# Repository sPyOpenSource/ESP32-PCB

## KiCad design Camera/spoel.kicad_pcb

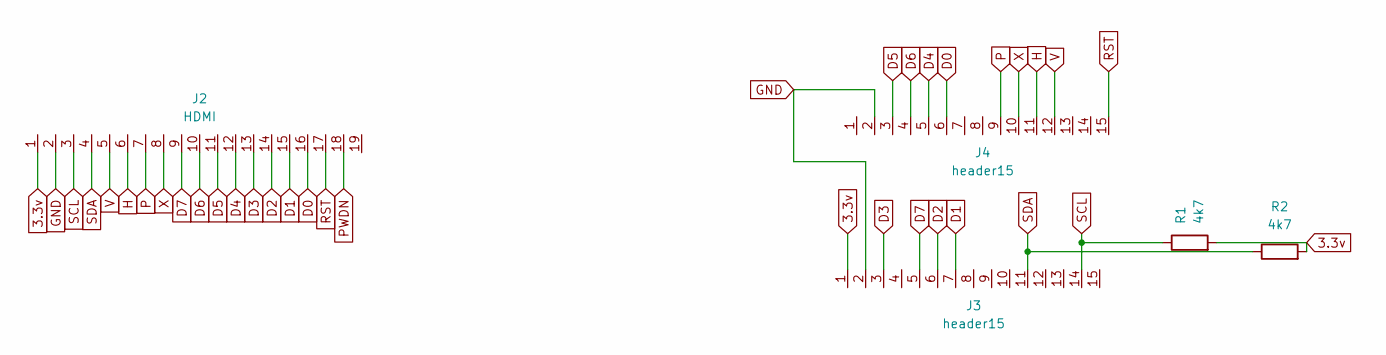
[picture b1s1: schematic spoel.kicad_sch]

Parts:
J2: HDMI; PinSocket_2x09_P2.54mm_Vertical
J3, J4: header15; PinHeader_1x15_P2.54mm_Horizontal
R1, R2: 4k7; R_0603_1608Metric

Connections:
3.3v: J2.1, J3.1, R1.2, R2.2
D0: J2.16, J4.6
D1: J2.15, J3.7
D2: J2.14, J3.6
D3: J2.13, J3.3
D4: J2.12, J4.5
D5: J2.11, J4.3
D6: J2.10, J4.4
D7: J2.9, J3.5
GND: J2.2, J3.2, J4.2
H: J2.6, J4.11
P: J2.7, J4.9
PWDN: J2.18
RST: J2.17, J4.15
SCL: J2.3, J3.14, R1.1
SDA: J2.4, J3.11, R2.1
V: J2.5, J4.12
X: J2.8, J4.10

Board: 4 copper layers, 5 parts (0 on the bottom side), 17 nets, no tracks yet.

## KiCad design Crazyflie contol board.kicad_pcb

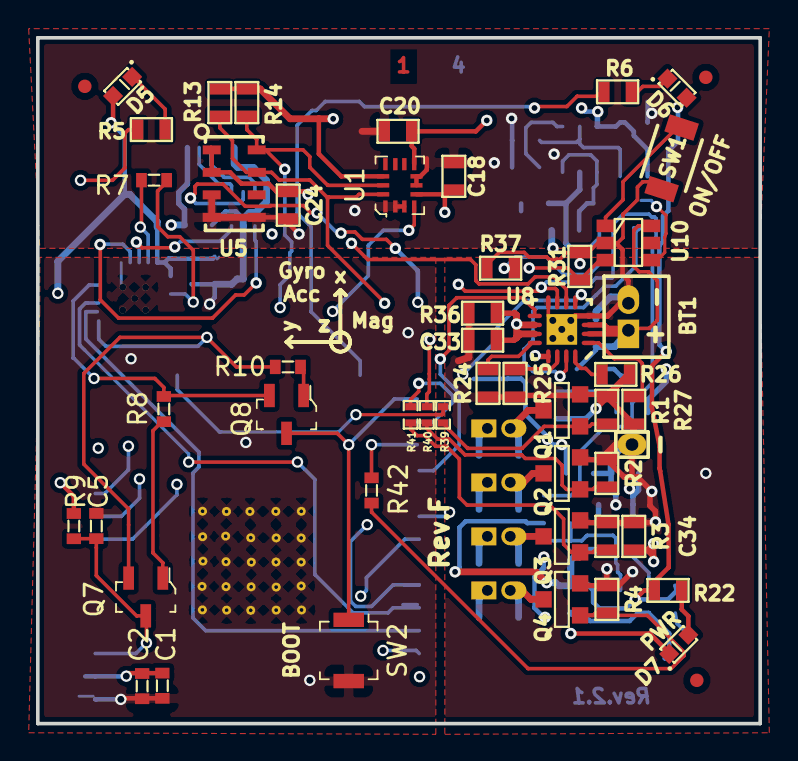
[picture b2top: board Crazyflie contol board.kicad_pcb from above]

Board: 4 copper layers, 40.1 x 38.1 mm, 92 parts (0 on the bottom side), 62 nets.

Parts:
BT1: BATTERY; JST-B2B-ZR
C1: 22uF; 0603_new_new
C2, C3, C5: 100nF; 0603_new_new
C4, C30, C31, C34, C37: 4.7uF; SM0603_Capa
C18, C20, C24, C33, C36, C38, C41: 100nF; SM0603_Capa
C29, C35: 15pF; SM0603_Capa
C32, C40: 10nF; SM0603_Capa
C39: 10uF; SM0603_Capa
D1, D2, D3, D4: BAT54; sod323
D5: RED LED; SMDLED-0603
D6: GREEN LED; SMDLED-0603
D7, D8: BLUE LED; SMDLED-0603
P1, P2, P3, P4: CONN_2; PINHEADER_127_2X1
P7: MICRO-B-USB; ZX62-B-5PA_11_CFK
P9: CONN_1; PINHEADER_127_1X1
Q1, Q2, Q3, Q4: PMV31XN; SOT23GDS
Q5, Q6: 2N7002; SOT23GDS
Q7, Q8: SS8050-G; SOT-23-3
R1, R2, R3, R4, R25, R27, R32, R33, R36, R37: 10k; SM0603
R5: 330R; SM0603
R6: 220R; SM0603
R7: 1k; 0603_new_new
R8, R9, R10: 10k; 0603_new_new
R13, R14: 2.2k; SM0603
R16: 39k; SM0603
R17: 10R; SM0603
R18, R28: 30k; SM0603
R19, R29: 0R; SM0603
R20: 42.2k; SM0603
R21: 300k; SM0603
R22, R38: 1k; SM0603
R23: 150k; SM0603
R24: 1.2k; SM0603
R26: 1.2K; SM0603
R30: 20k; SM0603
R31: 100k; SM0603
R39, R40, R41: 100R; SM0402
R42: 100R; 0603_new_new
SW1: PUSH ON/OFF; SPST-NO-4x2.5
SW2: BOOT; Switch_Tactile_SMD_B3U-1000P_new_new
U1: BMX160; LGA-14L_2.5x3mm__LSM6DS3
U5: MS5611-01BA03; MS5611
U6: NUF2221; SOT363
U7, U9: TPS79301; SOT23_6
U8: BQ24075; QFN16
U10: MAX16054; SOT23_6
U11: ESP32-WROOM; ESP32-WROOM-32_new
U12: CP2102N-A01-GQFN24; QFN-24-1EP_4x4mm_new_new_new

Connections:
+BATT: BT1.1, C39.1, D1.2, D2.2, D3.2, D4.2, P1.1, P2.1, P3.1, P4.1, R30.2, U8.2, U8.3, U10.6
/CHG: U8.9, U11.28
/EN1: U8.6, U11.10
/EN2: U8.5, U11.12
/I2C_SCK_VCCA: R13.2, U1.14, U5.7, U11.33
/I2C_SCL_VCCA: R14.2, U1.13, U5.8, U11.36
/INT_GA: U1.4, U11.9
/MOTOR1: R39.1, U11.16
/MOTOR2: R40.1, U11.37
/MOTOR3: R41.1, U11.26
/MOTOR4: R42.1, U11.27
/PGOOD: R21.1, R23.2, U8.7, U11.30
/POWER/D+: P7.3, U6.6
/POWER/D-: P7.2, U6.4
/POWER/VBAT: C41.1, Q5.S, R32.2
/POWER/VUSB: C36.1, P7.1, Q6.G, R37.2, U8.13
/RED: R5.1, U11.31
/SYSOFF: R31.2, U10.3, U11.8
/USBD+: U6.1, U12.3
/USBD-: U6.3, U12.4
AGND: C18.2, C20.2, C24.2, C30.2, C32.2, R18.1, R19.1, U1.1, U1.2, U1.3, U1.6, U1.7, U5.3, U5.4, U5.5
DGND: C1.2, C2.2, C3.1, C4.1, C5.1, C36.2, C37.2, C40.2, D7.2, D8.2, P7.5, R28.1, R29.1, SW2.2, U6.2, U11.1, U11.15, U11.38, U11.39, U12.2, U12.25
GND: BT1.2, C31.2, C33.2, C34.2, C38.2, C39.2, C41.2, P9.1, Q1.S, Q2.S, Q3.S, Q4.S, Q6.S, R1.2, R2.2, R3.2, R4.2, R19.2, R24.1, R25.1, R26.1, R27.1, R29.2, R31.1, R32.1, R36.1, R37.1, SW1.1, U7.2, U8.4, U8.8, U8.17, U9.2, U10.2
unnamed: C5.2, Q7.3, R9.2, U11.3
unnamed: C29.2, R16.1, R18.2, U7.5
unnamed: C31.1, R17.1, U7.1, U7.3
unnamed: C32.1, U7.4
unnamed: C35.2, R20.1, R23.1, R28.2, U9.5
unnamed: C40.1, U9.4
unnamed: D1.1, P1.2, Q1.D
unnamed: D2.1, P2.2, Q2.D
unnamed: D3.1, P3.2, Q3.D
unnamed: D4.1, P4.2, Q4.D
unnamed: D5.2, R5.2
unnamed: D6.2, R6.2
unnamed: D7.1, R22.1
unnamed: D8.1, R38.1
unnamed: Q1.G, R1.1, R39.2
unnamed: Q2.G, R2.1, R40.2
unnamed: Q3.G, R3.1, R41.2
unnamed: Q4.G, R4.1, R42.2
unnamed: Q5.D, R30.1
unnamed: Q6.D, R33.2, U8.15
unnamed: Q7.1, R8.1
unnamed: Q7.2, R10.1, U12.19
unnamed: Q8.1, R10.2
unnamed: Q8.2, R8.2, U12.23
unnamed: Q8.3, SW2.1, U11.25
unnamed: R6.1, U11.24
unnamed: R7.1, U12.5
unnamed: R7.2, U12.9
unnamed: R24.2, U8.12
unnamed: R25.2, U8.14
unnamed: R26.2, U8.16
unnamed: R27.2, U8.1
unnamed: R33.1, U10.4
unnamed: SW1.2, U10.1
unnamed: U11.34, U12.21
unnamed: U11.35, U12.20
VCC: C1.1, C2.1, C3.2, C4.2, C35.1, C37.1, D5.1, D6.1, R9.1, R20.2, R21.2, R22.2, R38.2, U6.5, U9.6, U11.2, U12.6, U12.7
VCCA: C18.1, C20.1, C24.1, C29.1, C30.1, R13.1, R14.1, R16.2, U1.5, U1.8, U1.12, U5.1, U5.2, U7.6
VCOM: C33.1, C34.1, C38.1, Q5.G, R17.2, R36.2, U8.10, U8.11, U9.1, U9.3

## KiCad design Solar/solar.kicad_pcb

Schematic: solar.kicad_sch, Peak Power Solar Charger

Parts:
C1, C4, C6, C15: 0.1uF; 0603
C2: 220uF; Cpol-6.3x7.7
C3: 100uF; Cpol-6.3x7.7
C5: 1nF; 0603
D1: D_Schottky; DO-214AC
D5: COMMS; 0603
IC1: MAX4173H
J1: SOLAR_INPUT; 1210
J2: Left; PIN16
J3: Right; PIN16
J4: BATTERY_OUTPUT; 1210
J5: header3; PIN2
J6: in; 1210
J7: SOLAR_OUTPUT; 1210
L2: 33uH; 7447779139
Q2: IRFIZ44N; SOT-223
R1, R2, R12: 10k; 0603
R3, R13, R14: 560R; 0603
R4: 100R; 0603
R7: 0.005R; 0603
R9: 4K7; R_0805_HandSoldering
R10: 220R; 0603
RX1: Receive; JST_PH_S2B-PH-K_02x2.00mm_Angled
RX2: Receive; PIN2
TX1: Transmit; JST_PH_S2B-PH-K_02x2.00mm_Angled
U1: HMHA2801; SOP-4_4.4x2.8mm_Pitch1.27mm
U2: MAX5424; TDFN-8-1EP

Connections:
+3V3: C1.1, IC1.1 (VCC), J3.1, RX1.2, U2.1
Bat+: C2.1, J4.1 (Bat+), J6.2, L2.2, R12.2; also elsewhere on the board
GND: C1.2, C2.2, C3.2, C4.2, C5.1, C6.2, C15.2, D1.2 (A), D5.1 (K), IC1.3 (GND), J1.2 (Sol-), J2.15, J3.2, J4.2 (Bat-), J6.1, J7.1 (Bat+), R1.2, R3.1, R9.1, R13.1, RX2.2, U1.2, U2.5; also elsewhere on the board
I_Sol: C4.1, IC1.4 (OUT), J2.6
unnamed: C5.2, Q2.1 (G), R1.1, R4.1
unnamed: D1.1 (K), L2.1, Q2.3 (S)
unnamed: D5.2 (A), R14.1
unnamed 7: IC1.8 (RS+), J1.1 (Sol+), R2.2, R7.1; also elsewhere on the board
unnamed: J2.12, U2.2
unnamed: J2.14, U2.3
unnamed: J3.3, U2.4
unnamed: J3.5, R14.2
unnamed: J3.10, RX2.1
unnamed: J3.12, R9.2, RX1.1
unnamed: J3.13, R10.2
unnamed: J5.1, U2.6
unnamed: J5.2, J5.6, U2.7
unnamed: J5.3, U2.8
unnamed: R10.1, U1.1
unnamed: TX1.1, U1.3
unnamed: TX1.2, U1.4
PWM: J3.15, R4.2
Solar+: C3.1, IC1.6 (RS-), J2.16, J7.2 (Bat-), Q2.2 (D), R7.2; also elsewhere on the board
U_Bat: C15.1, J2.8, R12.1, R13.2
U_Sol: C6.1, J2.5, R2.1, R3.2

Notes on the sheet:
Step Down DC to DC Converter
Solar Input between 7-12V
ESP32
Sensor like https://www.dfrobot.com/product-580.html (work in progress)

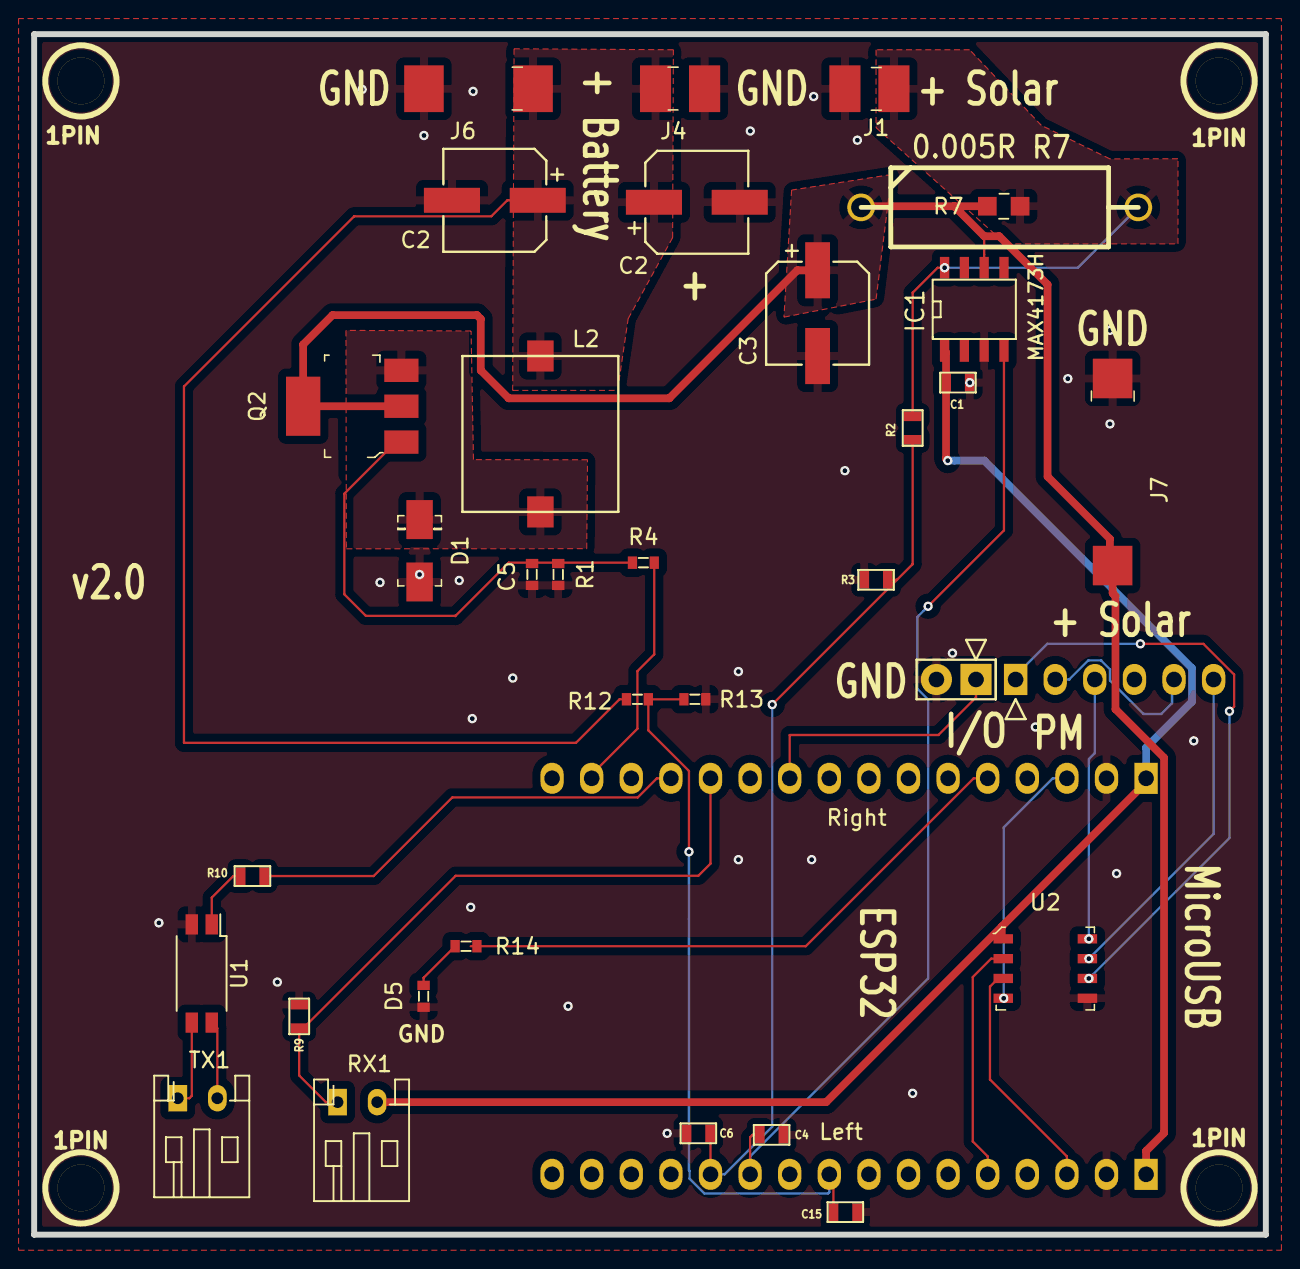
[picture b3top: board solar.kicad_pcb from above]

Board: 2 copper layers, 79.0 x 77.0 mm, 40 parts (0 on the bottom side), 25 nets.

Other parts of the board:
1PIN, 1PIN#2, 1PIN#3, 1PIN#4: 1pin
C2#2: 220uF; Cpol-6.3x7.7
R7#2: 0805

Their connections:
Bat+: C2#2.1; also elsewhere on the board
GND: C2#2.2; also elsewhere on the board
unnamed 7: R7#2.1; also elsewhere on the board
Solar+: R7#2.2; also elsewhere on the board

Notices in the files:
Crazyflie contol board.kicad_pcb:
Bitcraze AB (CC BY-NC-SA)
